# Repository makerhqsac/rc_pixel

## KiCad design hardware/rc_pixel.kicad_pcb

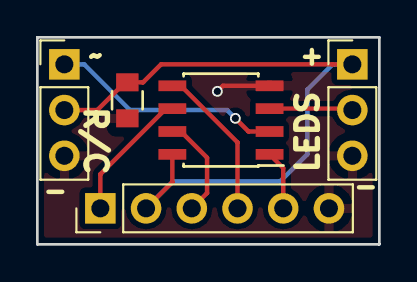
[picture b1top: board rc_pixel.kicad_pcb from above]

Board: 2 copper layers, 19.0 x 11.5 mm, 5 parts (0 on the bottom side), 8 nets.

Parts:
C1: C; C_0805
J1, J2: Conn_01x03; Pin_Header_Straight_1x03_Pitch2.54mm
J3: Conn_01x06; Pin_Header_Straight_1x06_Pitch2.54mm
U1: ATTINY85-20SU; SOIC-8_3.9x4.9mm_Pitch1.27mm

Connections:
+5V: C1.1, J1.2, J2.1, J3.2, U1.8
/LEDS: J2.2, U1.3
/MISO: J3.1, U1.6
/MOSI: J3.4, U1.5
/RC: J1.1, U1.2
/RST: J3.5, U1.1
/SCK: J3.3, U1.7
GND: C1.2, J1.3, J2.3, J3.6, U1.4

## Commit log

2018-03-06 first code
2018-03-06 Clean up cmake
2018-03-06 Add turn signal project
2018-03-11 fix signal issues finally
2018-03-11 code cleanup
2018-03-11 change pins to match board
